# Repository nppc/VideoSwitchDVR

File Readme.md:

# Control Board for Eachine Pro DVR (to install to EV100 Goggles)

Eachine Pro DVR using separate pins for input and output video signal. This makes it difficult to connect to EV100, where only one pin used for video in and out.

This board helps to automate the switching of video signal in DVR for playback or recording according to EV100 mode.

Also this board delays a startup of DVR for preventing cropping of PAL recording.

There is two additional pads (K1, K3), that can be used for controlling 2 buttons of DVR.

## Current functionality
- When Goggles are powered, power to the DVR is delayed, preventing cropping of recorded video (known as PAL cropping issue).
- If Goggles is in normal mode (signal is coming from VRX), then DVR is receiving the VRX signal.
- If Goggles in AV mode (signal coming from AVin), then DVR starts to send own video to the Goggles.
- Stop recording when Goggles are powered OFF (need to add supercapacitor).
- DVR buttons control: (start recording on power on, switch recording/playback mode automatically).

## Current version of the board

## Installed in the Goggles

## Power
I'm not sure how powerful is Goggle's DC/DC. So, it is safer to power DVR with additional DC/DC directly from Goggles battery.

Currently I'm using DIY 1A DC/DC with 5.2v output. It's switching frequency is 1.6Mhz, and has no noise in recorded video.

## Connection to the Goggles.
TODO.

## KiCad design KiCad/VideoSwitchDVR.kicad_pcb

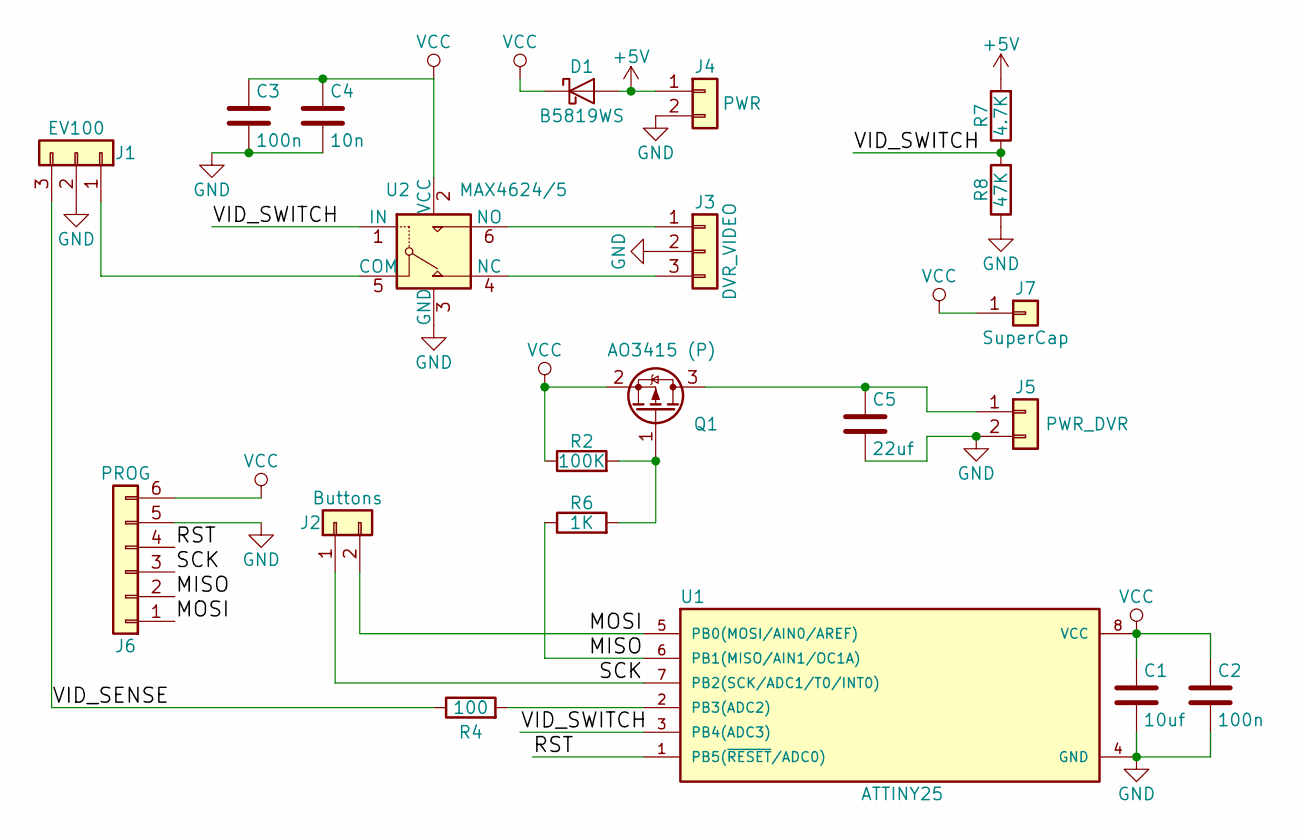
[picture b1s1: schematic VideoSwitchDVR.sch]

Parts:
C1: 10uf; C_0603
C2, C3: 100n; C_0603
C4: 10n; C_0603
C5: 22uf; C_0805
D1: B5819WS; D_SOD-323
J1: EV100; USB_3_PADS
J2: Buttons; POWER2PIN
J3: DVR_VIDEO; USB_3_PADS
J4: PWR; POWER2PIN
J5: PWR_DVR; POWER2PIN
J6: PROG; Pads_prog_6pin1.25mm
J7: SuperCap; ESC_PWR_PAD
Q1: AO3415 (P); SOT-23
R2: 100K; R_0603
R4: 100; R_0603
R6: 1K; R_0603
R7: 4.7K; R_0603
R8: 47K; R_0603
U1: ATTINY25; SOIJ-8_5.3x5.3mm_Pitch1.27mm
U2: MAX4624/5; SOT-23-6

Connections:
+5V: D1.2 (A), J4.1, R7.2
/MISO: J6.2, R6.1, U1.6 (PB1(MISO/AIN1/OC1A))
/MOSI: J2.2, J6.1, U1.5 (PB0(MOSI/AIN0/AREF))
/RST: J6.4, U1.1 (PB5(~RESET~/ADC0))
/SCK: J2.1, J6.3, U1.7 (PB2(SCK/ADC1/T0/INT0))
/VID_SENSE: J1.3, R4.1
/VID_SWITCH: R7.1, R8.2, U1.3 (PB4(ADC3)), U2.1 (IN)
GND: C1.2, C2.2, C3.2, C4.2, C5.2, J1.2, J3.2, J4.2, J5.2, J6.5, R8.1, U1.4 (GND), U2.3 (GND)
unnamed: C5.1, J5.1, Q1.3 (D)
unnamed: J1.1, U2.5 (COM)
unnamed: J3.1, U2.6 (NO)
unnamed: J3.3, U2.4 (NC)
unnamed: Q1.1 (G), R2.2, R6.2
unnamed: R4.2, U1.2 (PB3(ADC2))
VCC: C1.1, C2.1, C3.1, C4.1, D1.1 (K), J6.6, J7.1, Q1.2 (S), R2.1, U1.8 (VCC), U2.2 (VCC)

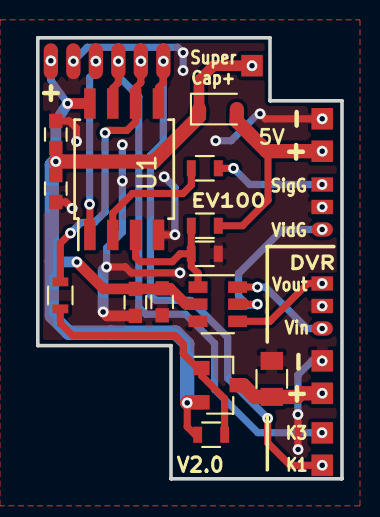
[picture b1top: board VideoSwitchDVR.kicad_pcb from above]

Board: 2 copper layers, 16.9 x 24.5 mm, 21 parts (0 on the bottom side), 15 nets.

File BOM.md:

## Bill of Materials

Ref | Value | size/footprint
-------- | ---------------- | ----------
U1 | ATTINY25, ATTINY45 or ATTINY85 | SOIC8
U2 | MAX4624 | SOT-23-6
R2 | 100K | 0603
R4 | 100 | 0603
R6 | 1K | 0603
R7 | 4.7K | 0603
R8 | 47K | 0603
C1 | 10uf | 0603
C2, C3 | 100n | 0603
C4 | 10n | 0603
C5 | 22uf | 0805
D1 | B5819WS (or any with 1A If) | SOD-323
Q1 | AO3415 | SOT-23

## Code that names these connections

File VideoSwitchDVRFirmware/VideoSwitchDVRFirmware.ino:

//#define DEBUG // Debug board (pins routed different)
//#define MODECHANGE_PLAYRECORD // Change DVR mode according to Goggles mode (normal/AV)
#define START_RECORDING // Start recording on power on.
//#define POWERLOSS_STOPRECORDING // Stop recording on power loss.

#define POWERON_DELAY 2000	//ms

// EV100 VIdeo sense signal is HIGH if in AVIN mode
#ifdef DEBUG
	#define PIN_SWITCH_VIDEO 	0	//PB0
	#define PIN_EV100_SIG		3 	//PB3
	#define PIN_DVR_K1			1 	//PB1 (DEBUG LED)
	#define PIN_DVR_K3 			4	//PB4
	#define PIN_DVR_POWER		2	//PB2 (LED)
#else
	#define PIN_SWITCH_VIDEO 	4	//PB4
	#define PIN_EV100_SIG		3 	//PB3
	#define PIN_DVR_K1 			0	//PB0 start/stop recording
	#define PIN_DVR_K3 			2	//PB2 3sec press - enter playback mode
	#define PIN_DVR_POWER		1	//PB1
#endif

#define EV100AV (1<<PIN_EV100_SIG)	// AV Mode when pin PIN_EV100_SIG is HIGH
	
// Pressing button for 2 seconds toggles DVR mode (Record/Playback)
#ifdef DEBUG
	#define LED_DEBUG_ON bitClear(PORTB, PIN_DVR_K1) // LED ON
	#define LED_DEBUG_OFF bitSet(PORTB, PIN_DVR_K1) // LED OFF
#else
	#define DVR_K1_OFF bitClear(DDRB, PIN_DVR_K1) // Button released
	#define DVR_K1_ON bitSet(DDRB, PIN_DVR_K1) // Button pressed
#endif
// Start/stop recording
#define DVR_K3_OFF bitClear(DDRB, PIN_DVR_K3) // Button released
#define DVR_K3_ON bitSet(DDRB, PIN_DVR_K3) // Button pressed
#define DVR_POWER_ON bitClear(PORTB, PIN_DVR_POWER) // DVR POWER ON
#define DVR_POWER_OFF bitSet(PORTB, PIN_DVR_POWER) // DVR POWER OFF

uint8_t DVR_state;	// 0 - recording; anything else - playback
uint8_t EV100_state = 0;

void setup()
{
	DVR_POWER_OFF; // DVR Power is OFF
	bitSet(DDRB,PIN_DVR_POWER);	//  port as output
#ifndef DEBUG
	bitClear(PORTB,PIN_DVR_K1);	// control DVR
	DVR_K1_OFF;
#endif
	bitClear(PORTB,PIN_DVR_K3);	// control DVR
	DVR_K3_OFF;
	bitClear(DDRB,PIN_EV100_SIG);	// listen for signal level pin
	// PIN_SWITCH_VIDEO has a double function.
	// We are listening for power loss and switching video in/out.
	// We need to listen only while recording. So, AVin should be connected when PIN_SWITCH_VIDEO is high (default).
	// PIN_SWITCH_VIDEO is pulled up by Goggle power.
	bitClear(PORTB, PIN_SWITCH_VIDEO); // Video Switch default video from EV100 to DVR (recording)
	bitClear(DDRB, PIN_SWITCH_VIDEO); // Listening for power loss...
	
	#ifdef DEBUG
		// when not connected to EV100. Later we remove pullup.
		bitSet(PORTB, PIN_EV100_SIG); //PullUp
		bitSet(DDRB, PIN_DVR_K1);
		LED_DEBUG_OFF;
	#endif
	
	DVR_state = 0; // After power on we are in recording mode

	#ifdef DEBUG
		LED_DEBUG_ON;
	#endif		
	delay(POWERON_DELAY);
	#ifdef DEBUG
		LED_DEBUG_OFF;
	#endif		
	DVR_POWER_ON;

	#ifdef START_RECORDING
		startRecording();	// delay and start recording
	#endif
	
	ReadEV100state();	// update EV100state variable
}


void loop() {
	// listen for signal level
	ReadEV100state();
	
	// turn video switch according to EV100 state
	if(EV100_state==EV100AV){
		//Active Low
		//bitClear(PORTB, PIN_SWITCH_VIDEO);
		bitSet(DDRB, PIN_SWITCH_VIDEO);
	}else{
		//Floating (Pulled up by external resistor)
		bitClear(DDRB, PIN_SWITCH_VIDEO);
		//bitClear(PORTB, PIN_SWITCH_VIDEO);
	}
	
#ifdef MODECHANGE_PLAYRECORD
	if(EV100_state==EV100AV){
		// switch DVR to PLAY mode. Pressing K3 button for 3 seconds will stop recording and go to PLAY mode.
		DVR_K3_ON;
		#ifdef DEBUG
		LED_DEBUG_ON;
		#endif
		delay(3000);
		DVR_K3_OFF;
		#ifdef DEBUG
		LED_DEBUG_OFF;
		#endif		
		DVR_state=1;	//play
	}else{
		// EV100 mode is normal. Need to  determine, are we just switched from AV?
		if(DVR_state!=0){
			// we need to reboot DVR to make 100% switch to recording mode
			DVR_POWER_OFF;
			delay(2000);
			DVR_POWER_ON;
			DVR_state=0; //record
			#ifdef START_RECORDING
				// If needed let's start recording.
				startRecording();
			#endif
		}
	}
#endif

#ifdef POWERLOSS_STOPRECORDING
	// sense PIN_SWITCH_VIDEO pin only while EV100 in normal mode. If low, then stop recording as soon as possible
	if(EV100_state==0){ // check for power loss only while recording
		if((PINB & (1<<PIN_SWITCH_VIDEO))==0){
			// stop recording
			#ifdef DEBUG
				LED_DEBUG_ON;
			#endif		
			DVR_K1_ON;
			delay(200);
			#ifdef DEBUG
				LED_DEBUG_OFF;
			#endif		
			DVR_K1_OFF;
			while(1){}; //wait until supercapacitor will be empty
		}
	}
#endif
      
	
}


void ReadEV100state(){
	uint8_t new_state = (PINB & (1<<PIN_EV100_SIG));
	delay(50);
	if(new_state == (PINB & (1<<PIN_EV100_SIG))){EV100_state=new_state;}
}

#ifdef START_RECORDING
void startRecording(){
	delay(9000);	// wait while DVR is booting and will be ready for recording
	DVR_K1_ON;
	delay(200);
	DVR_K1_OFF;
}
#endif

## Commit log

2018-01-15 Add KiCad project
2018-01-16 Some progress on PCB. MCU changed to simplier one
2018-01-17 Test code for Attiny25
2018-03-22 Some work
2018-03-23 Work in progress
2018-03-23 invert logic of Video switch
2018-03-23 Now can use two buttons and power loss sensing at the same time
2018-03-24 Idea with combined sensning and video switch on one pin is working
2018-03-24 K1, K3 buttons are clarified
2018-03-26 Some references and pictures
2018-03-26 Schematic as png
2018-04-29 firmware for attiny15
2018-04-30 Firmware ported to attiny15
2018-04-30 alfa version is 90% tested
2018-05-03 PCB 2.0. Case SCAD.
2018-05-03 Readme
2018-05-07 3D printed case finished
2018-05-07 After first power ON we also need to wait for DVR boot
2018-07-28 Some changes to ASM firmware
2018-07-28 BOM and pdf schematic added
